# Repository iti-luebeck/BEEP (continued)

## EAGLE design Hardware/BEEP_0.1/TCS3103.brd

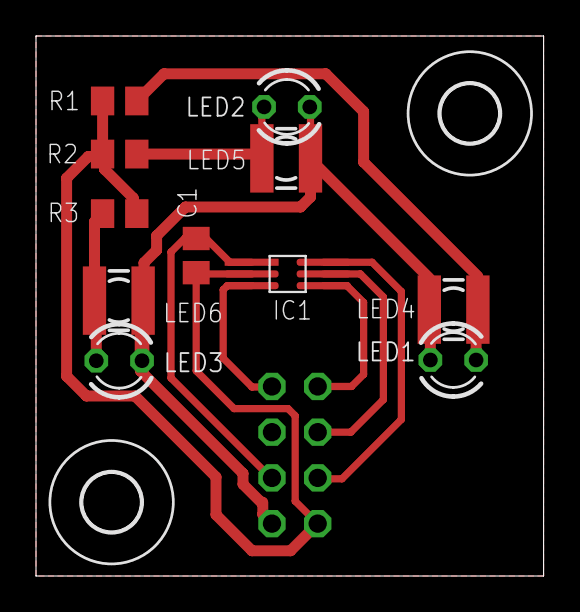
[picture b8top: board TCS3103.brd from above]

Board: 2 copper layers, 28.2 x 30.0 mm, 15 parts (1 on the bottom side), 10 nets.

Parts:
C1: 100n; C0805
IC1: TCS3103
JP1: 2X04
LED1, LED2, LED3: LED3MM
LED4, LED5, LED6: NFSG036BT
R1, R2, R3: M0805
U$1: LOGO-COPPER4; COPPER4
U$3, U$4: 3,2

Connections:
GND: C1.2, IC1.GND, JP1.7, R1.2, R2.2, R3.2
unnamed: IC1.VOB, JP1.1
unnamed: IC1.VOG, JP1.3
unnamed: IC1.VOR, JP1.5
unnamed: IC1.MFP, JP1.2
unnamed: LED1.K, LED4.C, R1.1
unnamed: JP1.8, LED1.A, LED2.A, LED3.A, LED4.A, LED5.A, LED6.A
unnamed: LED3.K, LED6.C, R3.1
unnamed: LED2.K, LED5.C, R2.1
VCC: C1.1, IC1.VDD, JP1.6
